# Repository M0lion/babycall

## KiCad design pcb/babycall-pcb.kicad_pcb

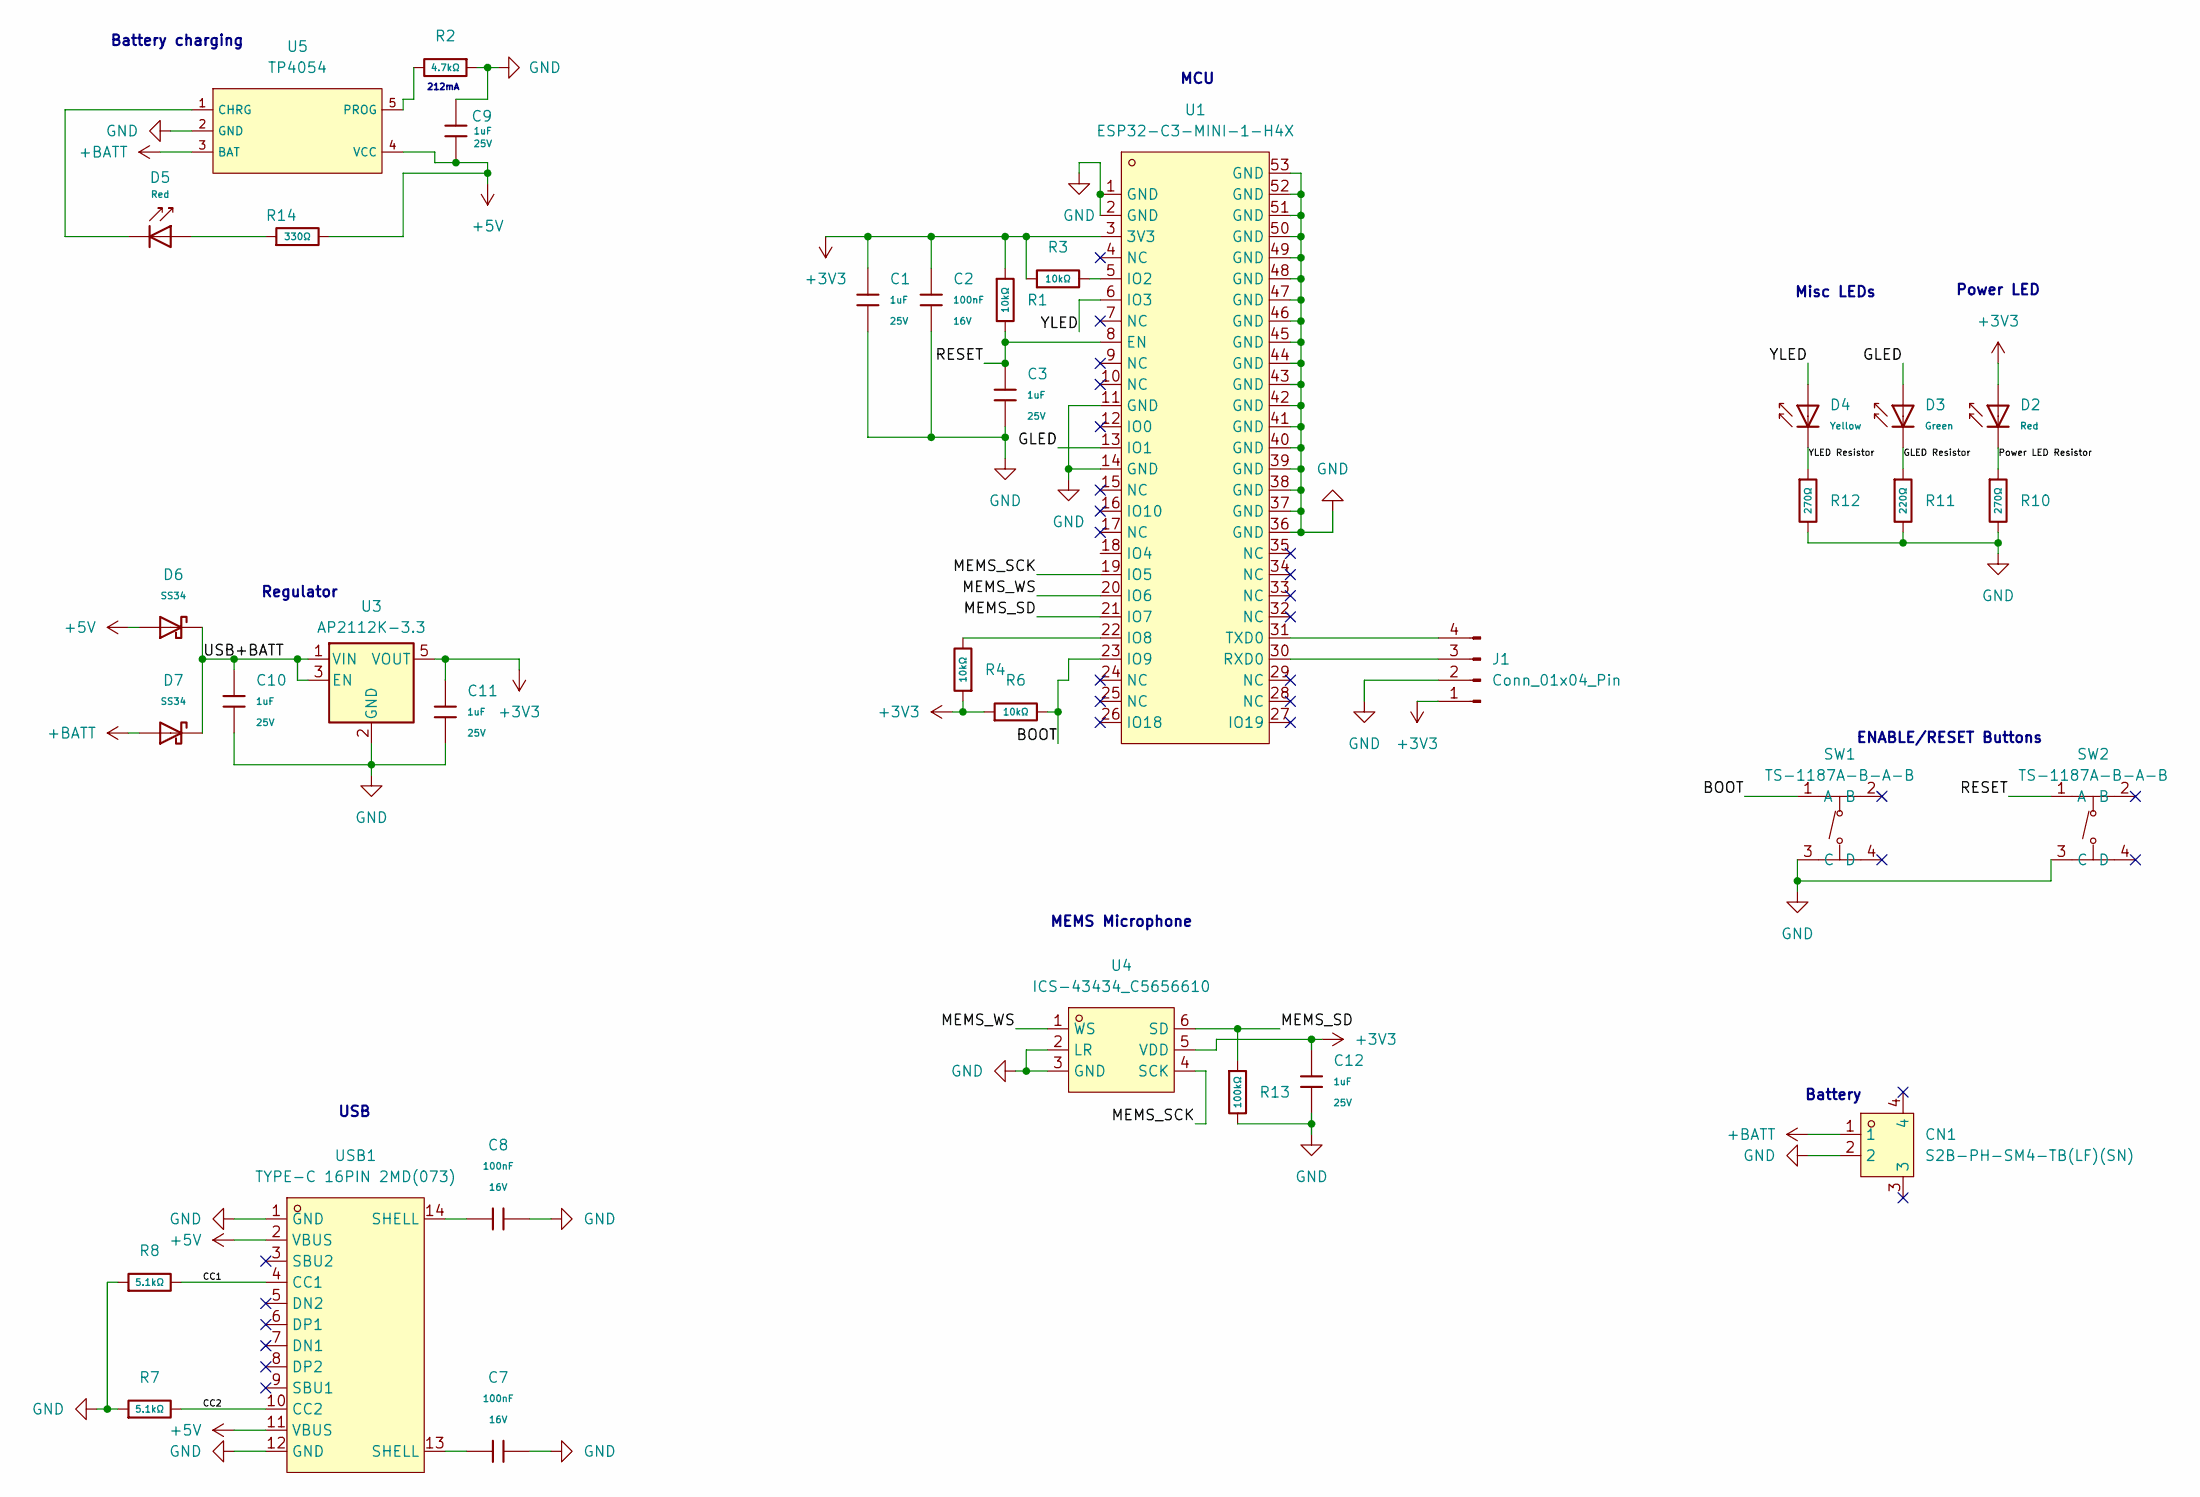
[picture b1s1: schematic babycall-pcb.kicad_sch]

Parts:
C1, C3, C9, C10, C11, C12: 1uF; C_0402; Voltage Rated 25V; Tolerance ±10%; Part CL05A105KA5NQNC; LCSC Part Number C52923
C2, C7, C8: 100nF; C_0402; Voltage Rated 16V; Tolerance ±10%; Part CL05B104KO5NNNC; LCSC Part Number C1525
CN1: S2B-PH-SM4-TB(LF)(SN); CONN-SMD_P2.00_S2B-PH-SM4-TB-LF-SN; LCSC Part Number C295747
D2, D5: Red; D_0603; Part KT-0603R; LCSC Part Number C2286
D3: Green; D_0805; Part KT-0805G; LCSC Part Number C2297
D4: Yellow; D_0603; Forward Voltage (VF) 1.6V~2.6V; Part NCD0603Y2; LCSC Part Number C89811
D6, D7: SS34; D_SMA; Forward Voltage (Vf@If) 0.55V@3.0A; Reverse Voltage (Vr) 40V; Part SS34; LCSC Part Number C7420365
J1: Conn_01x04_Pin; PinHeader_1x04_P2.54mm_Vertical
R1, R3, R4, R6: 10kΩ; R_0402; Overload Voltage (Max) 50V; Tolerance ±1%; Part 0402WGF1002TCE; LCSC Part Number C25744
R2: 4.7kΩ; R_0402; Overload Voltage (Max) 50V; Tolerance ±1%; Part 0402WGF4701TCE; LCSC Part Number C25900
R7, R8: 5.1kΩ; R_0402; Overload Voltage (Max) 50V; Tolerance ±1%; Part 0402WGF5101TCE; LCSC Part Number C25905
R10, R12: 270Ω; R_0603; Overload Voltage (Max) 75V; Tolerance ±1%; Part 0603WAF2700T5E; LCSC Part Number C22966
R11: 220Ω; R_0402; Overload Voltage (Max) 50V; Tolerance ±1%; Part 0402WGF2200TCE; LCSC Part Number C25091
R13: 100kΩ; R_0402; Overload Voltage (Max) 50V; Tolerance ±1%; Part 0402WGF1003TCE; LCSC Part Number C25741
R14: 330Ω; R_0402; Overload Voltage (Max) 50V; Tolerance ±1%; Part 0402WGF3300TCE; LCSC Part Number C25104
SW1, SW2: TS-1187A-B-A-B; SW-SMD_4P-L5.1-W5.1-P3.70-LS6.5-TL_H1.5; LCSC Part Number C318884
U1: ESP32-C3-MINI-1-H4X; WIFIM-SMD_ESP32-C3-MINI-1; LCSC Part Number C41349510
U3: AP2112K-3.3; SOT-23-5; LCSC Part Number C23380830
U4: ICS-43434_C5656610; MIC-SMD_6P-L3.5-W2.7-P0.90-BL; LCSC Part Number C5656610
U5: TP4054; SOT-23-5_L3.0-W1.7-P0.95-LS2.8-BL; Part TP4054-42-SOT25R; LCSC Part Number C32574
USB1: TYPE-C 16PIN 2MD(073); USB-C-SMD_TYPE-C-6PIN-2MD-073; LCSC Part Number C2765186

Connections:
+3V3: C1.1, C2.1, C11.1, C12.1, D2.2, J1.1, R1.1, R3.1, R4.1, R6.1, U1.3 (3V3), U3.5 (VOUT), U4.5 (VDD)
+5V: C9.2, D6.2, R14.2, U5.4 (VCC), USB1.2 (VBUS), USB1.11 (VBUS)
+BATT: CN1.1, D7.2, U5.3 (BAT)
/BOOT: R6.2, SW1.1 (A), U1.23 (IO9)
/CC1: R8.2, USB1.4 (CC1)
/CC2: R7.2, USB1.10 (CC2)
/GLED: D3.2, U1.13 (IO1)
/GLED Resistor: D3.1, R11.1
/MEMS_SCK: U1.19 (IO5), U4.4 (SCK)
/MEMS_SD: R13.1, U1.21 (IO7), U4.6 (SD)
/MEMS_WS: U1.20 (IO6), U4.1 (WS)
/Power LED Resistor: D2.1, R10.1
/RESET: C3.1, R1.2, SW2.1 (A), U1.8 (EN)
/USB+BATT: C10.2, D6.1, D7.1, U3.1 (VIN), U3.3 (EN)
/YLED: D4.2, U1.6 (IO3)
/YLED Resistor: D4.1, R12.1
GND: C1.2, C2.2, C3.2, C7.2, C8.2, C9.1, C10.1, C11.2, C12.2, CN1.2, J1.2, R2.1, R7.1, R8.1, R10.2, R11.2, R12.2, R13.2, SW1.3 (C), SW2.3 (C), U1.1 (GND), U1.2 (GND), U1.11 (GND), U1.14 (GND), U1.36 (GND), U1.37 (GND), U1.38 (GND), U1.39 (GND), U1.40 (GND), U1.41 (GND), U1.42 (GND), U1.43 (GND), U1.44 (GND), U1.45 (GND), U1.46 (GND), U1.47 (GND), U1.48 (GND), U1.49 (GND), U1.50 (GND), U1.51 (GND), U1.52 (GND), U1.53 (GND), U3.2 (GND), U4.2 (LR), U4.3 (GND), U5.2 (GND), USB1.1 (GND), USB1.12 (GND)
unnamed: C7.1, USB1.13 (SHELL)
unnamed: C8.1, USB1.14 (SHELL)
unnamed: D5.2, R14.1
unnamed: J1.3, U1.30 (RXD0)
unnamed: J1.4, U1.31 (TXD0)
unnamed: R3.2, U1.5 (IO2)
unnamed: R4.2, U1.22 (IO8)
unnamed: D5.1, U5.1 (CHRG)
unnamed: R2.2, U5.5 (PROG)

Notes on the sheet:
212mA
Misc LEDs
USB
Battery
MCU
ENABLE/RESET Buttons
Regulator
MEMS Microphone
Battery charging
Power LED

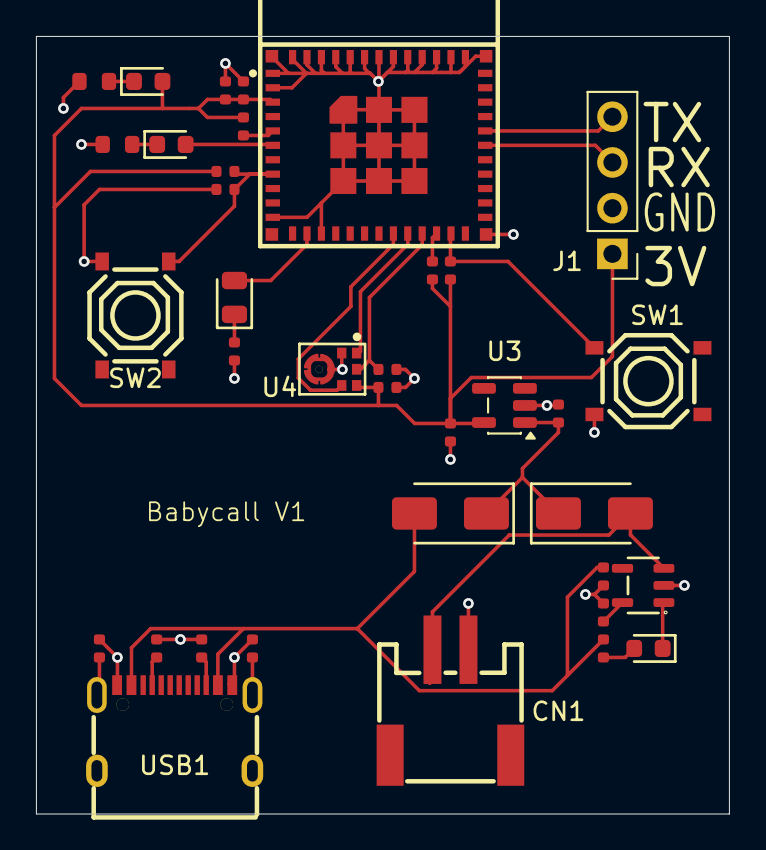
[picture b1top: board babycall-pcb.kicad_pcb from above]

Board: 2 copper layers, 38.5 x 43.2 mm, 36 parts (0 on the bottom side), 26 nets.

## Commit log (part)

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2026-01-08 BLE works!
2026-01-09 BLE audio choppy but working
2026-01-09 Better audio
2026-01-12 gain
2026-01-12 Schematic almost done
2026-01-12 Added usb cc resistors
2026-01-12 Working on schematic
2026-03-30 Claude stuff, and gitignore
    Also some models for pcb
2026-06-17 Claude did some shit?
